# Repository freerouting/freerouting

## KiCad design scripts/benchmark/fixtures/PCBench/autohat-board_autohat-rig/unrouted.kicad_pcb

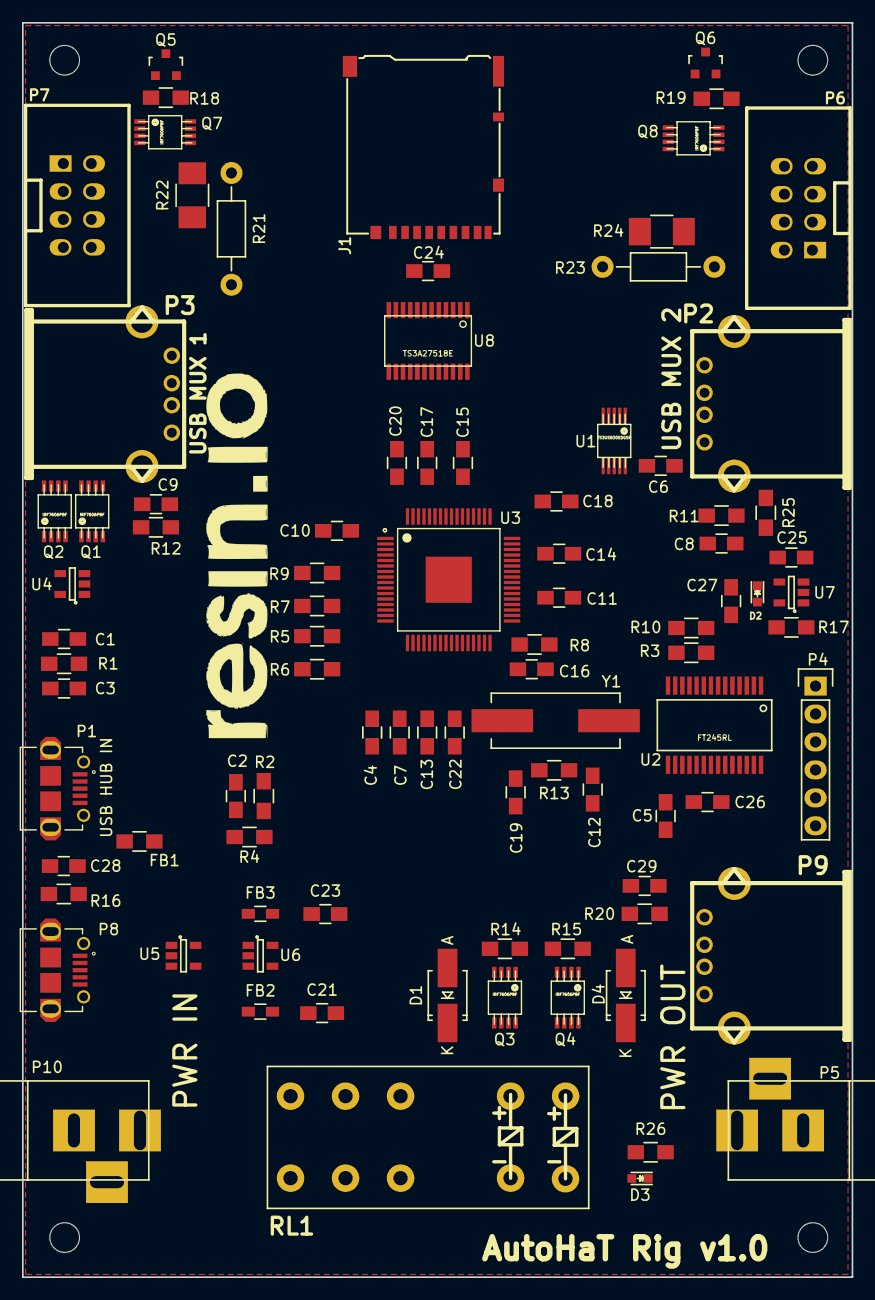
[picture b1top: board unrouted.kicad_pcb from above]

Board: 2 copper layers, 75.4 x 114.0 mm, 91 parts (0 on the bottom side), 78 nets, no tracks yet.

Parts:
C1, C5, C6, C7, C10, C11, C13, C14, C15, C16, C17, C18, C20, C22, C24, C25, C26: 100n; C_0805_HandSoldering
C2, C21, C23: 10u; C_0805_HandSoldering
C3: 1n; C_0805_HandSoldering
C4: 1u; C_0805_HandSoldering
C8, C9, C28, C29: 27p; C_0805_HandSoldering
C12, C19: 18p; C_0805_HandSoldering
C27: 4.7u; C_0805_HandSoldering
D1, D4: ES1A-LTP; SMA_Handsoldering
D2, D3: LED; LED_0603
FB1: MI0805K400R-10; R_0805_HandSoldering
FB2, FB3: BLM18PG221SN1D; R_0603_HandSoldering
J1: USDCARD; HIROSE-MICROSD-DM3AT-SF
P1: USB HUB IN; TO_microUSB
P2: USB MUX 2; conn_usb_A
P3: USB MUX 1; conn_usb_A
P4: CONN_01X06; Pin_Header_Straight_1x06
P5, P10: BARREL_JACK
P6, P7: IDC_02X04; PSB_IDC_4x2
P8: PWR IN; TO_microUSB
P9: PWR OUT; conn_usb_A
Q1, Q2, Q3, Q4, Q7, Q8: IRF7606PBF; msoic-8
Q5, Q6: 2N7002; SOT-23
R1, R13: 1M; R_0805_HandSoldering
R2: 90.9K; R_0805_HandSoldering
R3, R4, R10, R14, R15, R17, R18, R19, R25, R26: 10K; R_0805_HandSoldering
R5, R6, R7, R9, R11, R12, R16, R20: 4.7K; R_0805_HandSoldering
R8: 9.53K; R_0805_HandSoldering
R21, R23: 0; Resistor_Horizontal_RM10mm
R22, R24: 0; R_1210_HandSoldering
RL1: G2RK-2-DC5; G2RK-2
U1: TS3USB30EDGSR; msoic-10
U2: FT245RL; ssop-28
U3: TUSB4041IPAPR; QFP50P1200X1200X105-65N
U4, U7: 74AHC1G14; SOT-23-5
U5: TLV73333; SOT-23-5
U6: TLV73311; SOT-23-5
U8: TS3A27518E; tssop-24
Y1: 24MHz; Crystal_HC49-SD_SMD

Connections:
+3V3: C5.1, C24.1, C25.1, U2.17, U8.8
/1P1V: FB3.1, U6.5
/3P3V: FB2.1, U5.5, U6.1, U6.3
/CLK_DUT: P6.5, U8.23
/CLK_TS: P7.5, U8.15
/CMD_DUT: P6.3, U8.21
/CMD_TS: P7.3, U8.17
/DAT0_DUT: P6.7, U8.1
/DAT0_TS: P7.7, U8.13
/DAT1_DUT: P6.8, U8.2
/DAT1_TS: P7.8, U8.11
/DAT2_DUT: P6.1, U8.22
/DAT2_TS: P7.1, U8.16
/DAT3_DUT: P6.2, U8.19
/DAT3_TS: P7.2, U8.18
/POWER_SW_OFF: Q3.4, R14.2, U2.3
/POWER_SW_ON: Q4.4, R15.2, U2.2
/SOCKET_SEL: Q5.1, R17.2, U2.1, U7.2, U8.14, U8.24
/USB_DN1+: U2.15, U3.33
/USB_DN1-: U2.16, U3.34
/USB_DN2+: U1.4, U3.41
/USB_DN2-: U1.6, U3.42
/USB_MUX1+: P2.3, U1.2
/USB_MUX1-: P2.2, U1.8
/USB_MUX2+: P3.3, U1.3
/USB_MUX2-: P3.2, U1.7
/USB_SEL: Q1.4, R3.2, U1.1, U2.11, U4.2
/USB_UP+: P1.3, U3.21
/USB_UP-: P1.2, U3.22
/USB_VBUS: C2.1, FB1.2, P1.1, Q1.1, Q1.2, Q1.3, Q2.1, Q2.2, Q2.3, R2.1, U4.5, U5.1, U5.3
/USD_VDD: J1.4, Q7.5, Q7.6, Q7.7, Q7.8, Q8.5, Q8.6, Q8.7, Q8.8
/VDD_DUT: P6.4, R23.1, R24.1
/VDD_TS: P7.4, R21.1, R22.1
/XI: C12.1, R13.1, U3.30, Y1.1
/XO: C19.1, R13.2, U3.29, Y1.2
GND: C1.2, C2.2, C3.2, C4.1, C5.2, C6.2, C7.2, C8.2, C9.2, C10.2, C11.2, C12.2, C13.2, C14.2, C15.2, C16.2, C17.2, C18.2, C19.2, C20.2, C21.2, C22.2, C23.2, C24.2, C25.2, C26.2, C27.2, C28.2, C29.2, D1.2, D4.2, J1.6, P1.5, P2.4, P3.4, P4.1, P6.6, P7.6, Q5.3, Q6.3, R1.1, R4.1, R5.1, R6.1, R7.1, R8.1, R9.1, R11.2, R12.2, R16.2, R20.2, R25.1, R26.1, RL1.9, RL1.10, U1.5, U1.9, U2.7, U2.18, U2.21, U2.25, U2.26, U3.65, U4.3, U5.2, U6.2, U7.3, U8.5, U8.20
unnamed: C1.1, C3.1, P1.6, R1.2
unnamed: C4.2, U3.18
unnamed: C8.1, P2.5, R11.1
unnamed: C9.1, P3.5, R12.1
unnamed: C10.1, C13.1, C16.1, C18.1, C21.1, FB2.2, U3.2, U3.20, U3.31, U3.48
unnamed: C7.1, C11.1, C14.1, C15.1, C17.1, C20.1, C22.1, C23.1, FB3.2, U3.19, U3.25, U3.37, U3.45, U3.53, U3.60, U3.63
unnamed: C28.1, P8.6, R16.1
unnamed: C29.1, P9.5, R20.1
unnamed: D1.1, Q3.5, Q3.6, Q3.7, Q3.8, RL1.2
unnamed: D2.1, R25.2
unnamed: D2.2, Q6.1, U7.4
unnamed: D3.1, R26.2
unnamed: D3.2, D4.1, Q4.5, Q4.6, Q4.7, Q4.8, RL1.1
unnamed: J1.1, U8.12
unnamed: J1.2, U8.10
unnamed: J1.3, U8.9
unnamed: J1.5, U8.7
unnamed: J1.7, U8.6
unnamed: J1.8, U8.4
unnamed: P2.1, Q1.5, Q1.6, Q1.7, Q1.8
unnamed: P3.1, Q2.5, Q2.6, Q2.7, Q2.8
unnamed: P4.2, U2.5
unnamed: P4.3, U2.6
unnamed: P4.4, U2.9
unnamed: P4.5, U2.10
unnamed: P5.1, P9.1, RL1.4
unnamed: P5.2, P5.3, P9.4, RL1.7
unnamed: P8.1, P10.1, RL1.5
unnamed: P8.5, P10.2, P10.3, RL1.6
unnamed: Q2.4, U4.4
unnamed: Q5.2, Q7.4, R18.2
unnamed: Q6.2, Q8.4, R19.2
unnamed: Q7.1, Q7.2, Q7.3, R18.1, R21.2, R22.2
unnamed: Q8.1, Q8.2, Q8.3, R19.1, R23.2, R24.2
unnamed: R2.2, R4.2, U3.16
unnamed: R5.2, U3.13
unnamed: R6.2, U3.17
unnamed: R7.2, U3.10
unnamed: R8.2, U3.32
unnamed: R9.2, U3.8
unnamed: R10.2, U2.12
VDD: C6.1, C26.1, C27.1, FB1.1, P4.6, Q3.1, Q3.2, Q3.3, Q4.1, Q4.2, Q4.3, R3.1, R10.1, R14.1, R15.1, R17.1, U1.10, U2.4, U2.20, U7.5

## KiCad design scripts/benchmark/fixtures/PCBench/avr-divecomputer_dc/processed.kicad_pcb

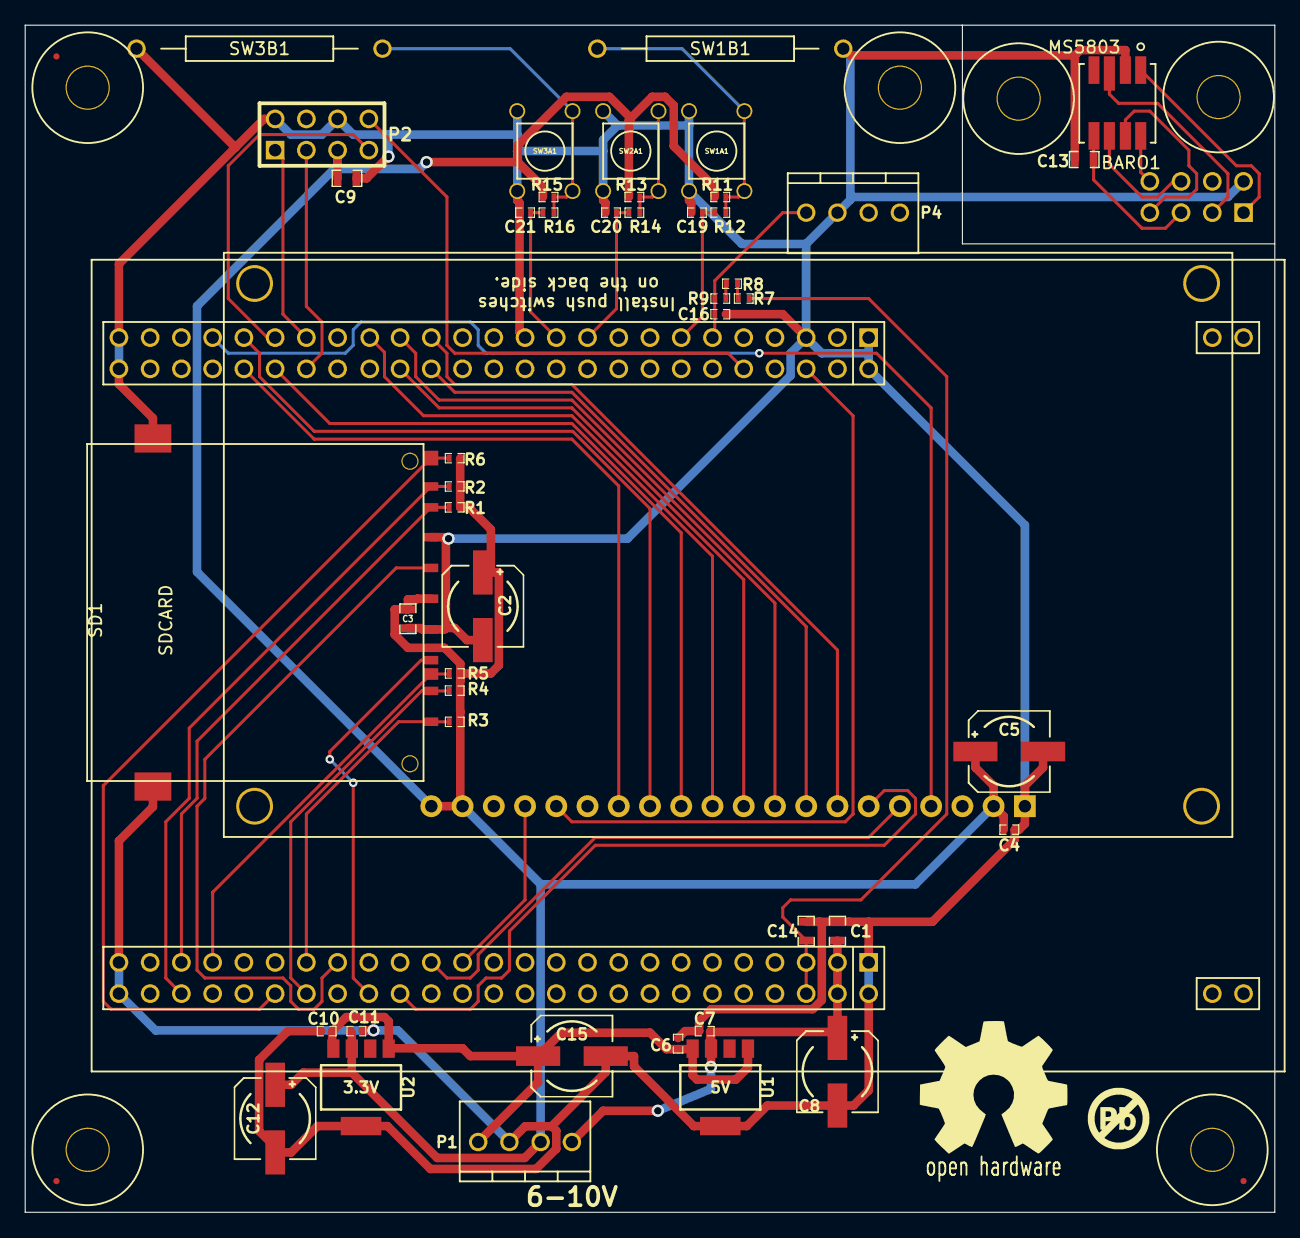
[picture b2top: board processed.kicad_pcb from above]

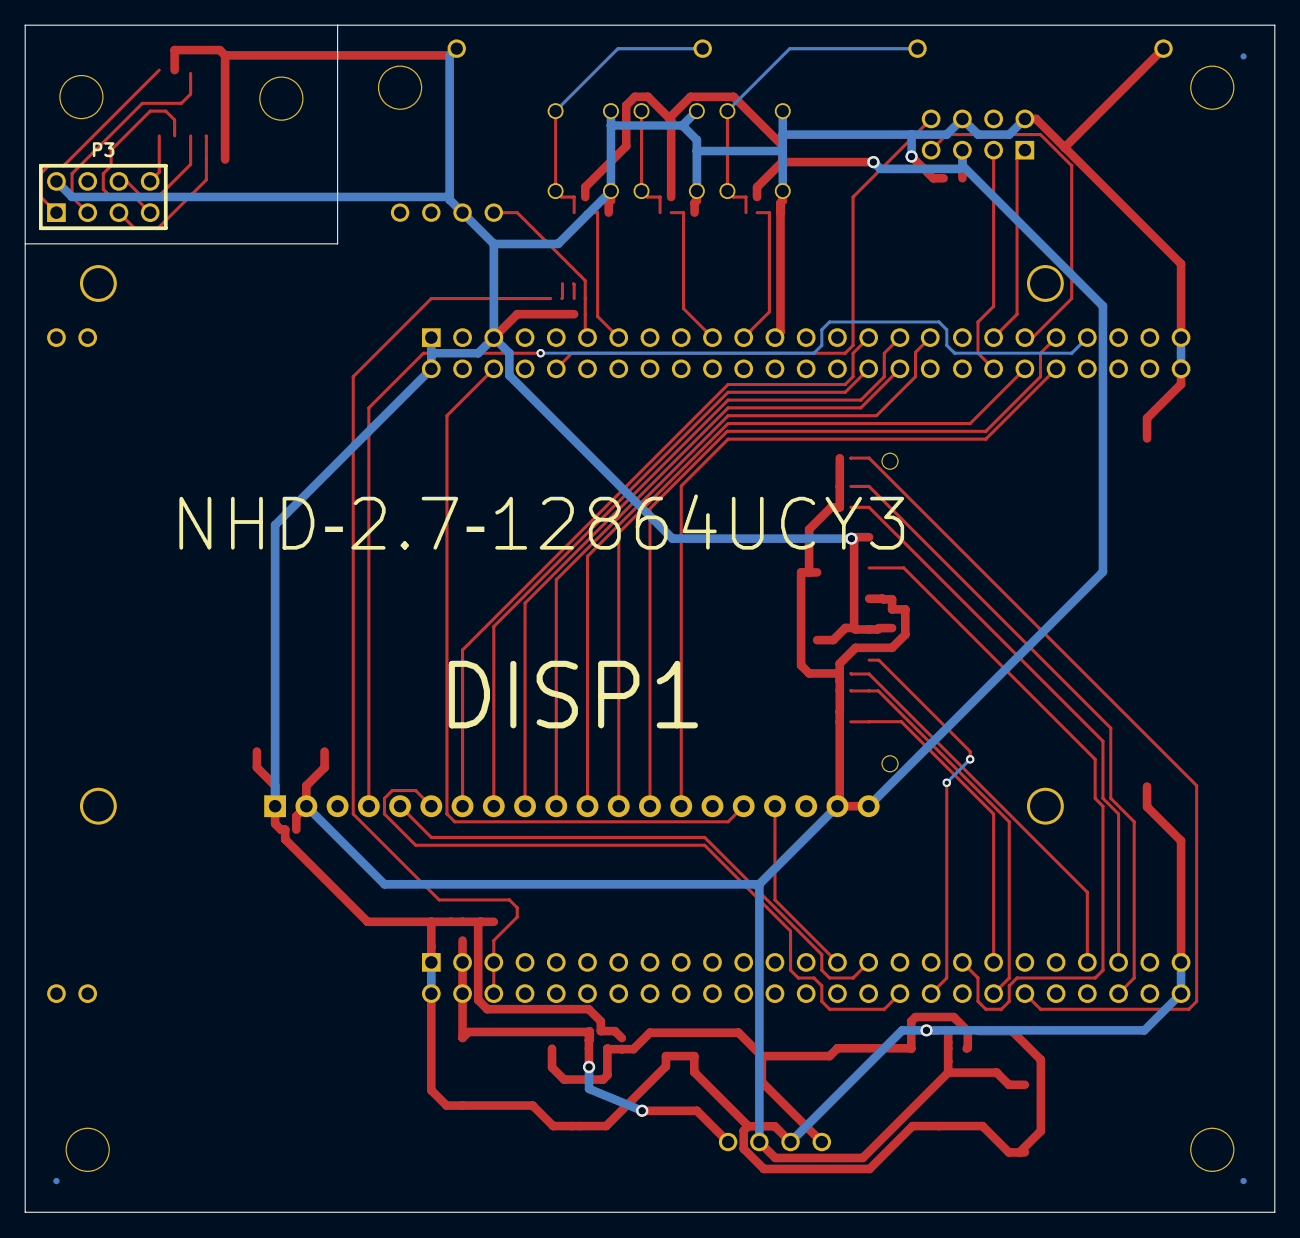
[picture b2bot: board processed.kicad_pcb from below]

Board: 2 copper layers, 101.6 x 96.5 mm, 58 parts (2 on the bottom side), 45 nets.

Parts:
BARO1: MS5803
C1, C3, C9, C13, C14: 10uF; SM0603_Capa
C2, C5, C8, C12, C15: 150uF; c_elec_6.3x5.7
C4, C6, C7, C10, C11, C16, C19, C20, C21: 1uF; SM0402_c
DISP1: NHD‐2.7‐12864UCY3
FID1: FID**; FIDUCIAL
FID2, FID3: VAL**; FIDUCIAL
J1: STM32F4_DISCOVERY_HEADER; stm32f4_discovery_header
M3_MOUNT, M3_MOUNT_2, M3_MOUNT_3, M3_MOUNT_4, M3_MOUNT_5, M3_MOUNT_6: VAL**; M3_MOUNT
P1, P4: CONN_4; ED10563-ND
P2, P3: CONN_4X2; pin_array_4x2
R1, R2, R3, R4, R5, R6, R7, R8, R9, R11, R12, R13, R14, R15, R16: 100k; SM0402
SD1: SDCARD; 101-00405-75-ND
SW1A1, SW2A1, SW3A1: SW_PUSH; P8008S-ND
SW1B1, SW3B1: SW_PUSH; REED
U1: 5V; SOT-223-5
U2: 3.3V; SOT-223-5

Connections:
+3.3V: C2.1, C3.1, C4.1, C5.1, C9.1, C11.1, C12.1, DISP1.2, DISP1.19, DISP1.20, P1.3, P2.5, R1.1, R2.1, R3.1, R4.1, R5.2, R6.2, R11.2, R13.2, R15.2, SD1.4, U2.3
+5V: C1.1, C7.1, C8.1, J1.97, J1.98, P1.4, U1.3
+BATT: C6.1, C10.1, C15.1, P1.1, U1.1, U1.4, U2.1, U2.4
DEPTH_CS: J1.38, P2.3
FSMC_A16: DISP1.4, J1.43
FSMC_D08: DISP1.7, J1.29
FSMC_D09: DISP1.8, J1.30
FSMC_D10: DISP1.9, J1.31
FSMC_D11: DISP1.10, J1.32
FSMC_D12: DISP1.11, J1.33
FSMC_D13: DISP1.12, J1.40
FSMC_D14: DISP1.13, J1.41
FSMC_D15: DISP1.14, J1.42
FSMC_NE1: DISP1.17, J1.73
FSMC_NOE: DISP1.6, J1.70
FSMC_NWE: DISP1.5, J1.71
GND: BARO1.2, C1.2, C2.2, C3.2, C4.2, C5.2, C6.2, C7.2, C8.2, C9.2, C10.2, C11.2, C12.2, C13.2, C14.2, C15.2, C16.2, C19.2, C20.2, C21.2, DISP1.1, J1.1, J1.2, J1.5, J1.23, J1.49, J1.50, J1.51, J1.52, J1.99, J1.100, P1.2, P2.2, P2.6, P3.2, P4.3, SD1.3, SD1.6, SD1.10, SW1A1.1, SW1B1.1, SW2A1.1, SW3A1.1, SW3B1.1, U1.5, U2.5
unnamed: R11.1, R12.1, SW1A1.2, SW1B1.2
unnamed: R7.1, R8.2
unnamed: R8.1, R9.1
unnamed: R13.1, R14.1, SW2A1.2
unnamed: R15.1, R16.1, SW3A1.2, SW3B1.2
unnamed: BARO1.8, P3.8
unnamed: BARO1.7, P3.7
unnamed: BARO1.6, P3.6
unnamed: BARO1.5, C13.1, P3.5
unnamed: BARO1.1, P3.1
unnamed: BARO1.3, P3.3
RESET: DISP1.16, J1.6
SDIO_CK: J1.65, SD1.5
SDIO_CMD: J1.68, SD1.2
SDIO_D0: J1.55, R1.2, SD1.7
SDIO_D1: J1.56, R2.2, SD1.8
SDIO_D2: J1.63, R3.2, SD1.9
SDIO_D3: J1.64, R4.2, SD1.1
SD_CD: J1.57, R5.1, SD1.11
SD_WP: J1.62, R6.1, SD1.12
SPI2_MISO: J1.10, P2.8
SPI2_MOSI: J1.39, P2.7
SPI2_SCK: J1.37, P2.1
STM_3V: C14.1, J1.95, J1.96, R7.2
SW1: C19.1, J1.13, R12.2
SW2: C20.1, J1.19, R14.2
SW3: C21.1, J1.21, R16.2
WATER: C16.1, J1.11, P4.4, R9.2

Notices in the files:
scripts/benchmark/fixtures/PCBench/autohat-board_autohat-rig/unrouted.kicad_pcb:
Copyright (c) 2016 Samsung Electronics Co., Ltd All Rights Reserved
